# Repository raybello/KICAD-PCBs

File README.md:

# KICAD-PCBs

A collection of KICAD PCB Design Files

2021

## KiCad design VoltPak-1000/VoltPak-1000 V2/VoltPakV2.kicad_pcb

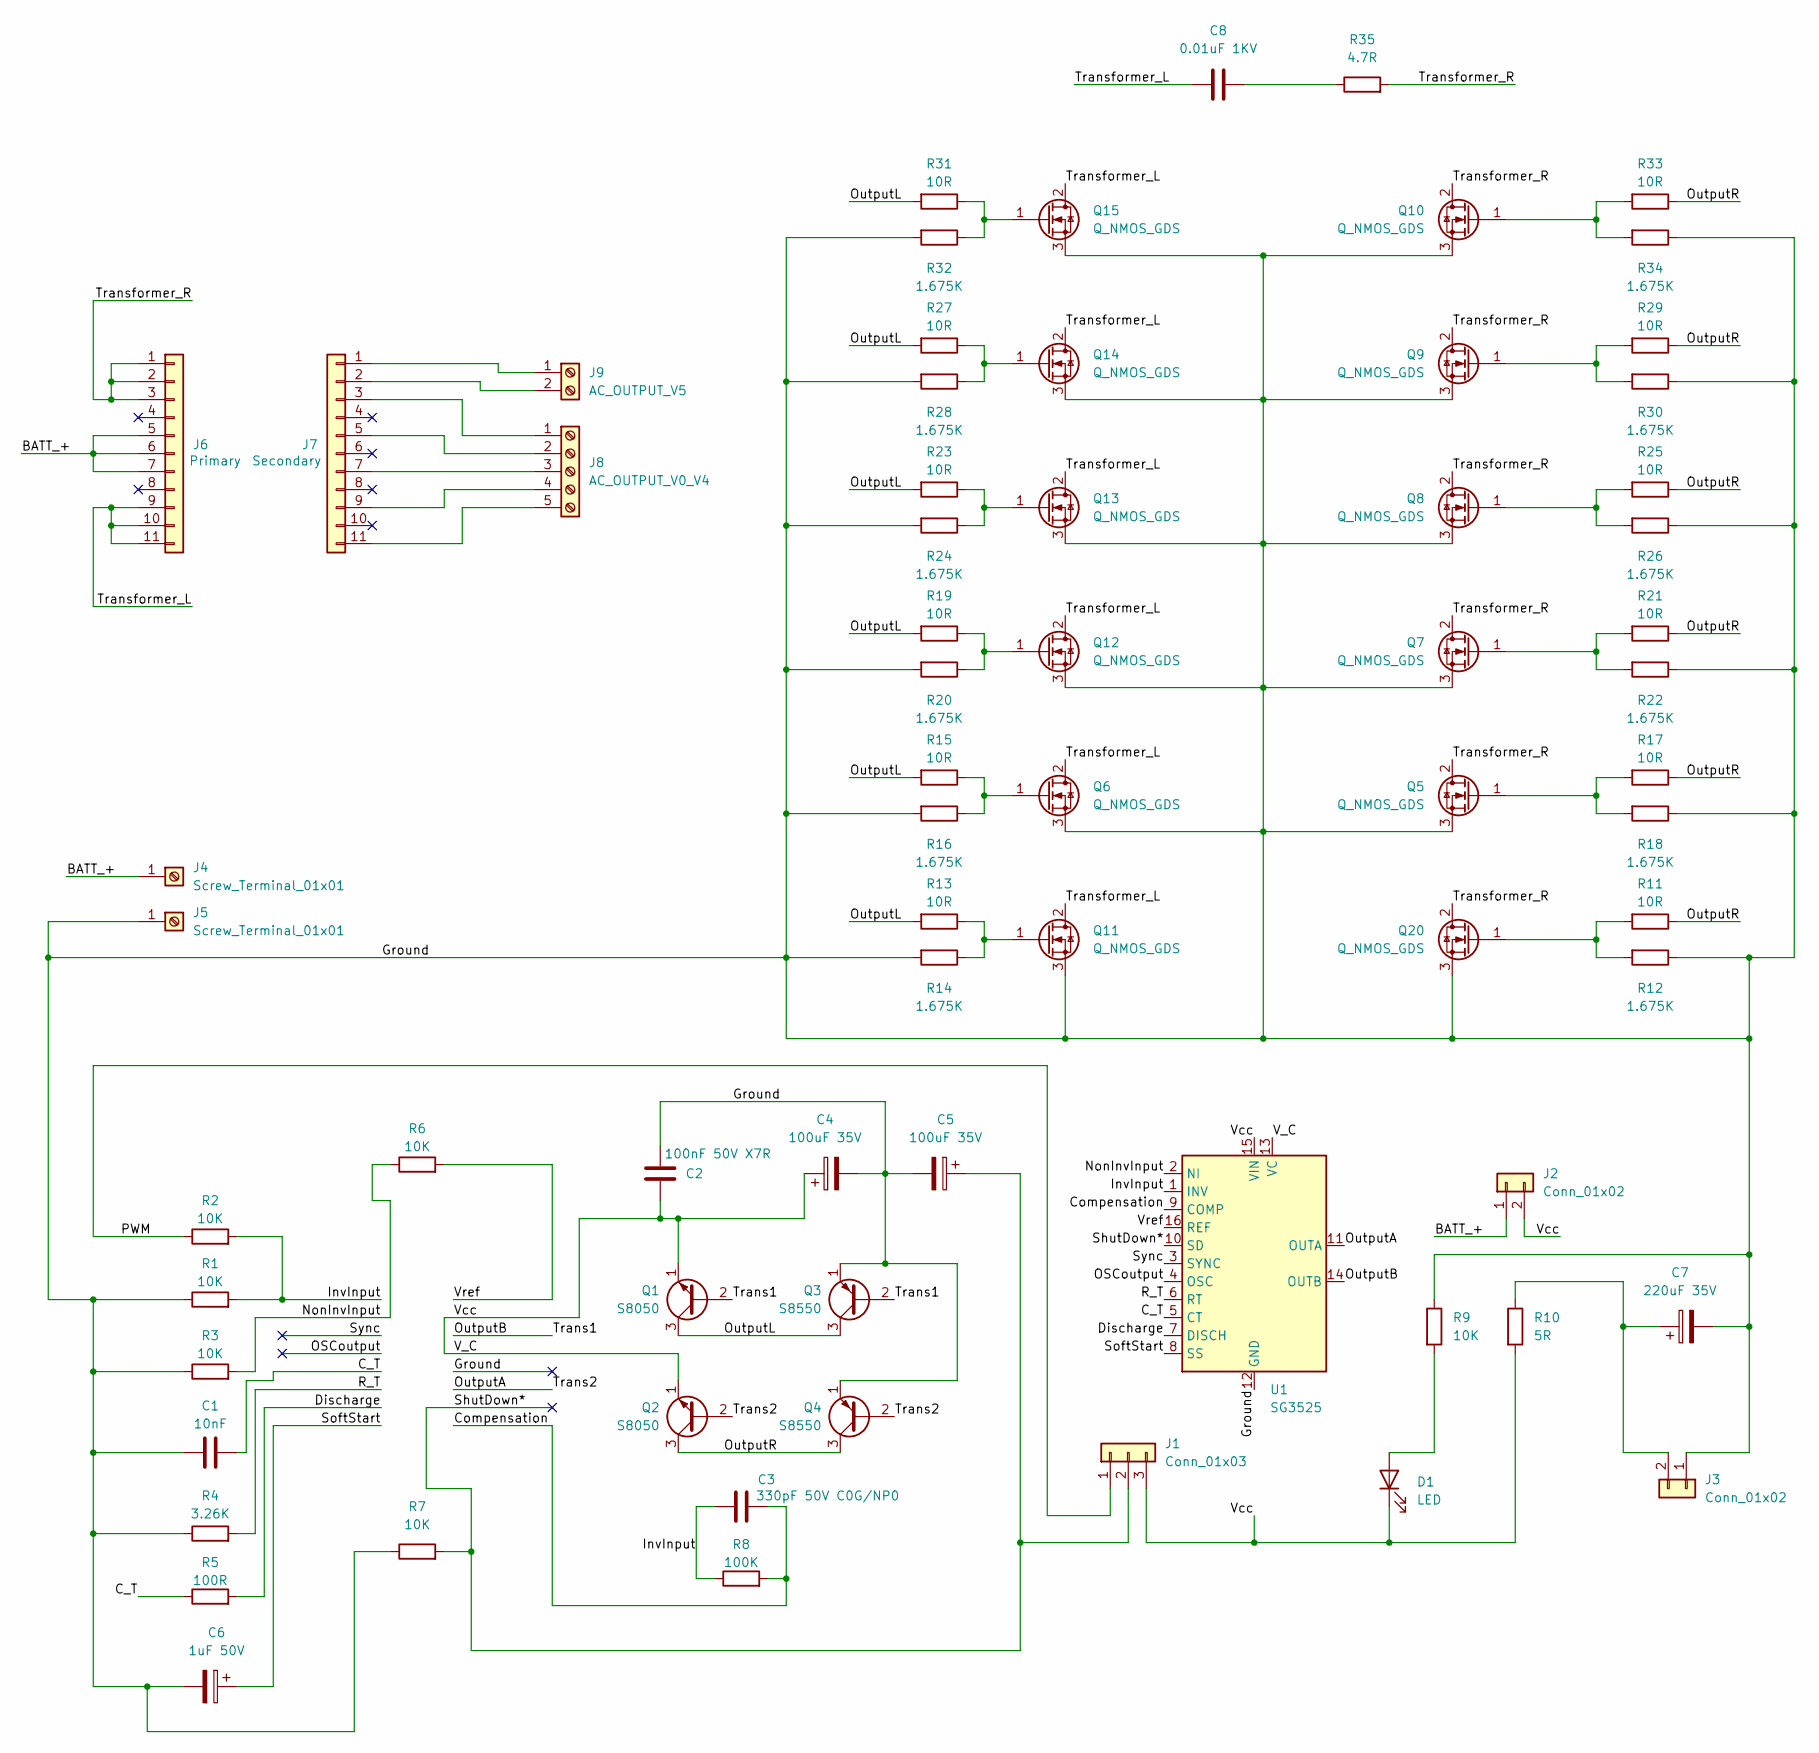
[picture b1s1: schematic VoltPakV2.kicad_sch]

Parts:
C1: 10nF; C_Disc_D4.7mm_W2.5mm_P5.00mm
C2: 100nF 50V X7R; C_Disc_D4.7mm_W2.5mm_P5.00mm
C3: 330pF 50V C0G/NP0; C_Disc_D4.7mm_W2.5mm_P5.00mm
C4, C5: 100uF 35V; CP_Radial_D6.3mm_P2.50mm
C6: 1uF 50V; CP_Radial_D5.0mm_P2.00mm
C7: 220uF 35V; CP_Radial_D8.0mm_P2.50mm
C8: 0.01uF 1KV; C_Disc_D4.7mm_W2.5mm_P5.00mm
D1: LED; LED_D3.0mm
J1: Conn_01x03; PinHeader_1x03_P2.54mm_Vertical
J2, J3: Conn_01x02; PinHeader_1x02_P2.54mm_Vertical
J4, J5: Screw_Terminal_01x01; TestPoint_THTPad_4.0x4.0mm_Drill2.0mm
J6: Primary; PinHeader_1x11_P2.54mm_Vertical
J7: Secondary; PinHeader_1x11_P2.54mm_Vertical
J8: AC_OUTPUT_V0_V4; PinSocket_1x05_P2.54mm_Vertical
J9: AC_OUTPUT_V5; PinSocket_1x02_P2.54mm_Vertical
Q1, Q2: S8050; TO-92_Inline
Q3, Q4: S8550; TO-92_Inline
Q5, Q6, Q7, Q8, Q9, Q10, Q11, Q12, Q13, Q14, Q15, Q20: Q_NMOS_GDS; TO-220-3_Vertical
R1, R2, R3, R6, R7, R9: 10K; R_0603_1608Metric
R4: 3.26K; R_0603_1608Metric
R5: 100R; R_0603_1608Metric
R8: 100K; R_0603_1608Metric
R10: 5R; R_0603_1608Metric
R11, R13, R15, R17, R19, R21, R23, R25, R27, R29, R31, R33: 10R; R_0603_1608Metric
R12, R14, R16, R18, R20, R22, R24, R26, R28, R30, R32, R34: 1.675K; R_0603_1608Metric
R35: 4.7R; R_0603_1608Metric
U1: SG3525; DIP-16_W7.62mm_Socket_LongPads

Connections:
/BATT_+: J2.1, J4.1, J6.5, J6.6, J6.7
/C_T: C1.2, R5.1, U1.5 (CT)
/Compensation: C3.1, R8.2, U1.9 (COMP)
/Discharge: R5.2, U1.7 (DISCH)
/Ground: C1.1, C2.1, C4.2, C5.2, C6.2, C7.2, J3.1, J5.1, Q3.1 (E), Q4.1 (E), Q5.3 (S), Q6.3 (S), Q7.3 (S), Q8.3 (S), Q9.3 (S), Q10.3 (S), Q11.3 (S), Q12.3 (S), Q13.3 (S), Q14.3 (S), Q15.3 (S), Q20.3 (S), R1.1, R3.1, R4.1, R7.1, R9.1, R12.1, R14.2, R16.2, R18.1, R20.2, R22.1, R24.2, R26.1, R28.2, R30.1, R32.2, R34.1, U1.12 (GND)
/InvInput: C3.2, R1.2, R2.2, R8.1, U1.1 (INV)
/NonInvInput: R3.2, R6.1, U1.2 (NI)
/OSCoutput: U1.4 (OSC)
/OutputA: Q2.2 (B), Q4.2 (B), U1.11 (OUTA)
/OutputB: Q1.2 (B), Q3.2 (B), U1.14 (OUTB)
/OutputL: Q1.3 (C), Q3.3 (C), R13.2, R15.2, R19.2, R23.2, R27.2, R31.2
/OutputR: Q2.3 (C), Q4.3 (C), R11.1, R17.1, R21.1, R25.1, R29.1, R33.1
/PWM: J1.1, R2.1
/R_T: R4.2, U1.6 (RT)
/ShutDown*: C5.1, J1.2, R7.2, U1.10 (SD)
/SoftStart: C6.1, U1.8 (SS)
/Sync: U1.3 (SYNC)
/Transformer_L: C8.1, J6.9, J6.10, J6.11, Q6.2 (D), Q11.2 (D), Q12.2 (D), Q13.2 (D), Q14.2 (D), Q15.2 (D)
/Transformer_R: J6.1, J6.2, J6.3, Q5.2 (D), Q7.2 (D), Q8.2 (D), Q9.2 (D), Q10.2 (D), Q20.2 (D), R35.2
/V_C: C2.2, C4.1, D1.1 (K), J1.3, J2.2, Q1.1 (E), Q2.1 (E), R10.2, U1.13 (VC), U1.15 (VIN)
/Vref: R6.2, U1.16 (REF)
unnamed: C8.2, R35.1
unnamed: D1.2 (A), R9.2
unnamed: C7.1, J3.2, R10.1
unnamed: J7.1, J9.1
unnamed: J7.2, J9.2
unnamed: J7.3, J8.1
unnamed: J7.5, J8.2
unnamed: J7.7, J8.3
unnamed: J7.9, J8.4
unnamed: J7.11, J8.5
unnamed: Q5.1 (G), R17.2, R18.2
unnamed: Q6.1 (G), R15.1, R16.1
unnamed: Q7.1 (G), R21.2, R22.2
unnamed: Q8.1 (G), R25.2, R26.2
unnamed: Q9.1 (G), R29.2, R30.2
unnamed: Q10.1 (G), R33.2, R34.2
unnamed: Q11.1 (G), R13.1, R14.1
unnamed: Q12.1 (G), R19.1, R20.1
unnamed: Q13.1 (G), R23.1, R24.1
unnamed: Q14.1 (G), R27.1, R28.1
unnamed: Q15.1 (G), R31.1, R32.1
unnamed: Q20.1 (G), R11.2, R12.2

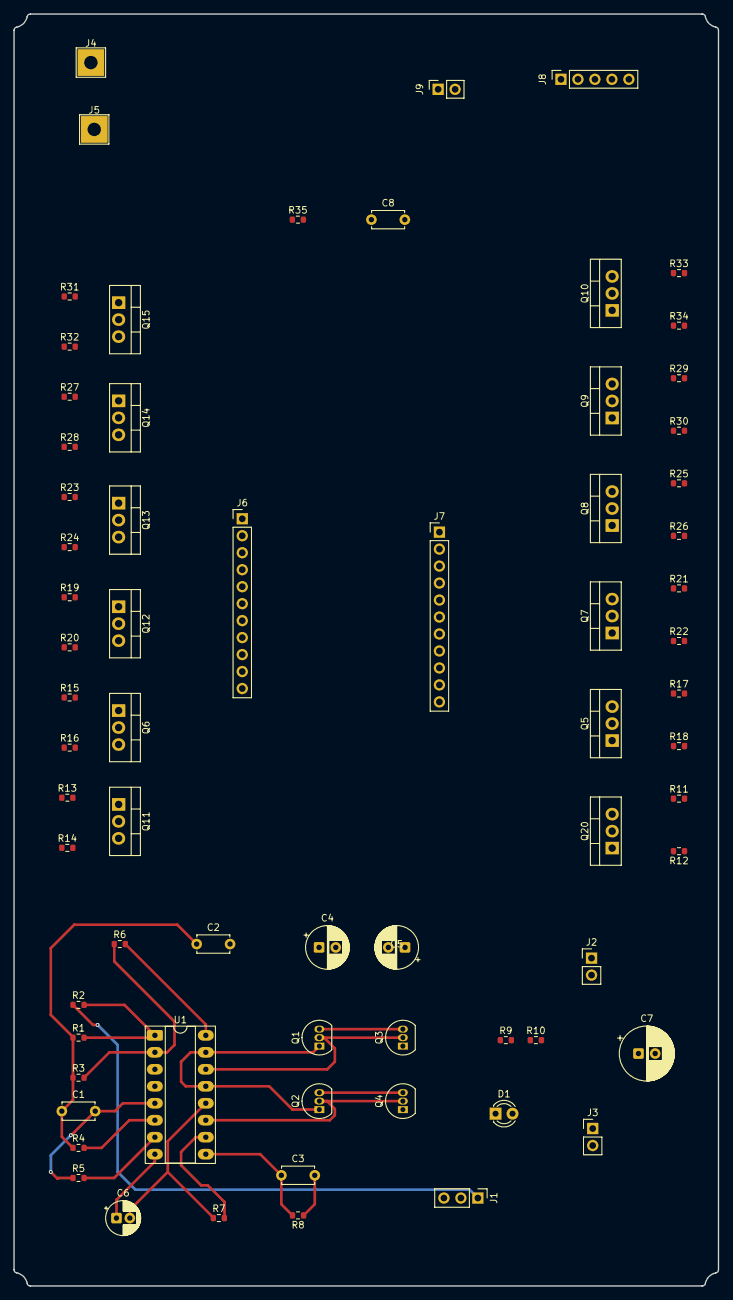
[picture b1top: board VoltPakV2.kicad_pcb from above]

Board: 2 copper layers, 105.4 x 190.3 mm, 70 parts (0 on the bottom side), 41 nets.

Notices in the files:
parts and their libraries:
Copyright 2021 Accelerated Designs. All rights reserved.
